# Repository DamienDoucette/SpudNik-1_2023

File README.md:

# SpudNik-1_2023
 Repo for the development of the control software for the UPEI CubeSat Project 2023S

 Created by Damien Doucette
 dldoucette@upei.ca
 damien.doucette01@gmail.com

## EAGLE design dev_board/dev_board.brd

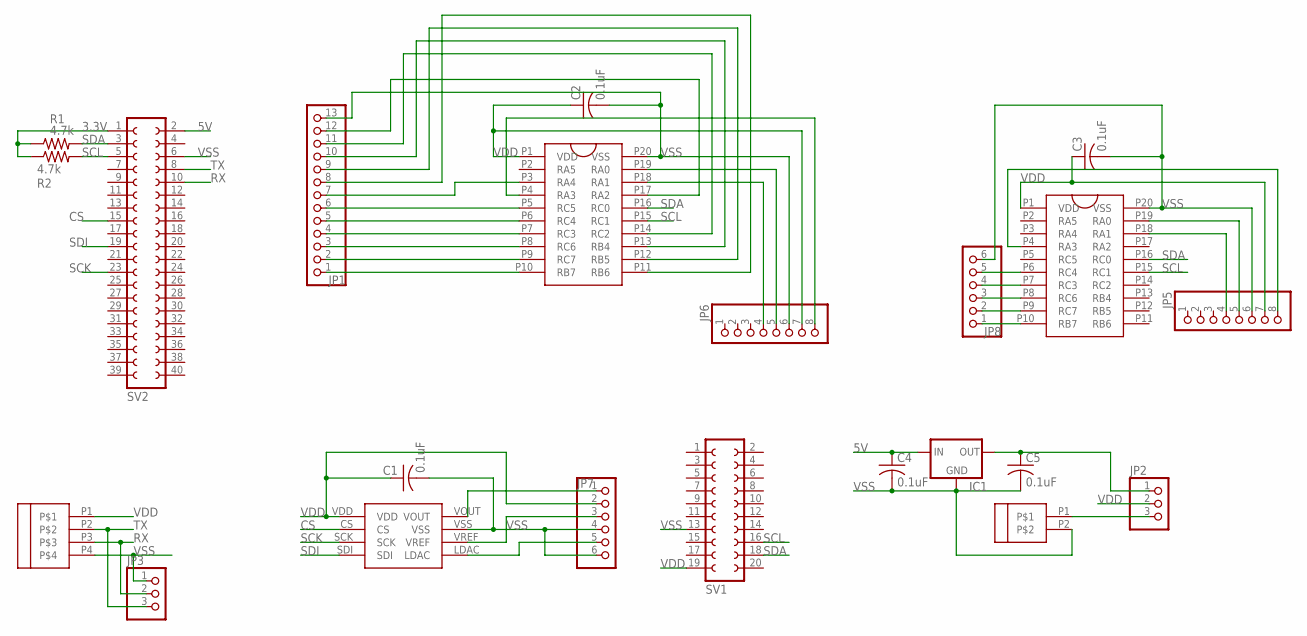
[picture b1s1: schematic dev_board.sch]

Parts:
C1, C2, C3, C4, C5: 0.1uF; C025-030X050
IC1: MCP1700INLINE; TO92-INLINE
JP1: PINHD-1X13; 1X13
JP2, JP3: PINHD-1X3; 1X03
JP5, JP6: PINHD-1X8BIG; 1X08-BIG
JP7, JP8: PINHD-1X6; 1X06
R1, R2: 4.7k; 0207/7
SV1: FE10-2
SV2: FE20-2
U1, U2: PIC18F15Q40PDIP; PDIP
U$1: MCP4911; DAC_DIP
U$2: 4TERMBLOCK
U$3: 2TERMBLOCK

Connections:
3.3V: R1.1, R2.1, SV2.1
5V: C4.1, IC1.2 (IN), SV2.2
CS: SV2.15, U$1.CS
unnamed: JP1.1, U1.P10 (RB7)
unnamed: JP1.2, U1.P9 (RC7)
unnamed: JP1.3, U1.P8 (RC6)
unnamed: JP1.4, U1.P7 (RC3)
unnamed: JP1.5, U1.P6 (RC4)
unnamed: JP1.6, U1.P5 (RC5)
unnamed: JP1.7, U1.P3 (RA4)
unnamed: JP6.8, U1.P4 (RA3)
unnamed: JP1.8, U1.P11 (RB6)
unnamed: JP2.3, U$3.P1
unnamed: JP6.5, U1.P19 (RA0)
unnamed: JP8.1, U2.P10 (RB7)
unnamed: JP8.2, U2.P9 (RC7)
unnamed: JP8.3, U2.P8 (RC6)
unnamed: JP8.4, U2.P7 (RC3)
unnamed: JP8.5, U2.P6 (RC4)
unnamed: JP6.4, U1.P18 (RA1)
unnamed: JP1.9, U1.P12 (RB5)
unnamed: JP1.10, U1.P13 (RB4)
unnamed: JP5.8, U2.P4 (RA3)
unnamed: JP5.5, U2.P19 (RA0)
unnamed: JP5.4, U2.P18 (RA1)
unnamed: JP7.5, U$1.LDAC
unnamed: JP1.11, U1.P14 (RC2)
unnamed: JP7.1, U$1.VOUT
unnamed: JP1.12, U1.P17 (RA2)
unnamed: JP7.3, U$1.VREF
unnamed: C5.1, IC1.3 (OUT), JP2.1
RX: JP3.2, SV2.10, U$2.P3
SCK: SV2.23, U$1.SCK
SCL: R2.2, SV1.16, SV2.5, U1.P15 (RC1), U2.P15 (RC1)
SDA: R1.2, SV1.18, SV2.3, U1.P16 (RC0), U2.P16 (RC0)
SDI: SV2.19, U$1.SDI
TX: JP3.3, SV2.8, U$2.P2
VDD: C1.1, C2.1, C3.1, JP2.2, JP5.7, JP6.7, JP7.2, SV1.19, U1.P1 (VDD), U2.P1 (VDD), U$1.VDD, U$2.P1
VSS: C1.2, C2.2, C3.2, C4.2, C5.2, IC1.1 (GND), JP1.13, JP3.1, JP5.6, JP6.6, JP7.4, JP7.6, JP8.6, SV1.13, SV2.6, U1.P20 (VSS), U2.P20 (VSS), U$1.VSS, U$2.P4, U$3.P2

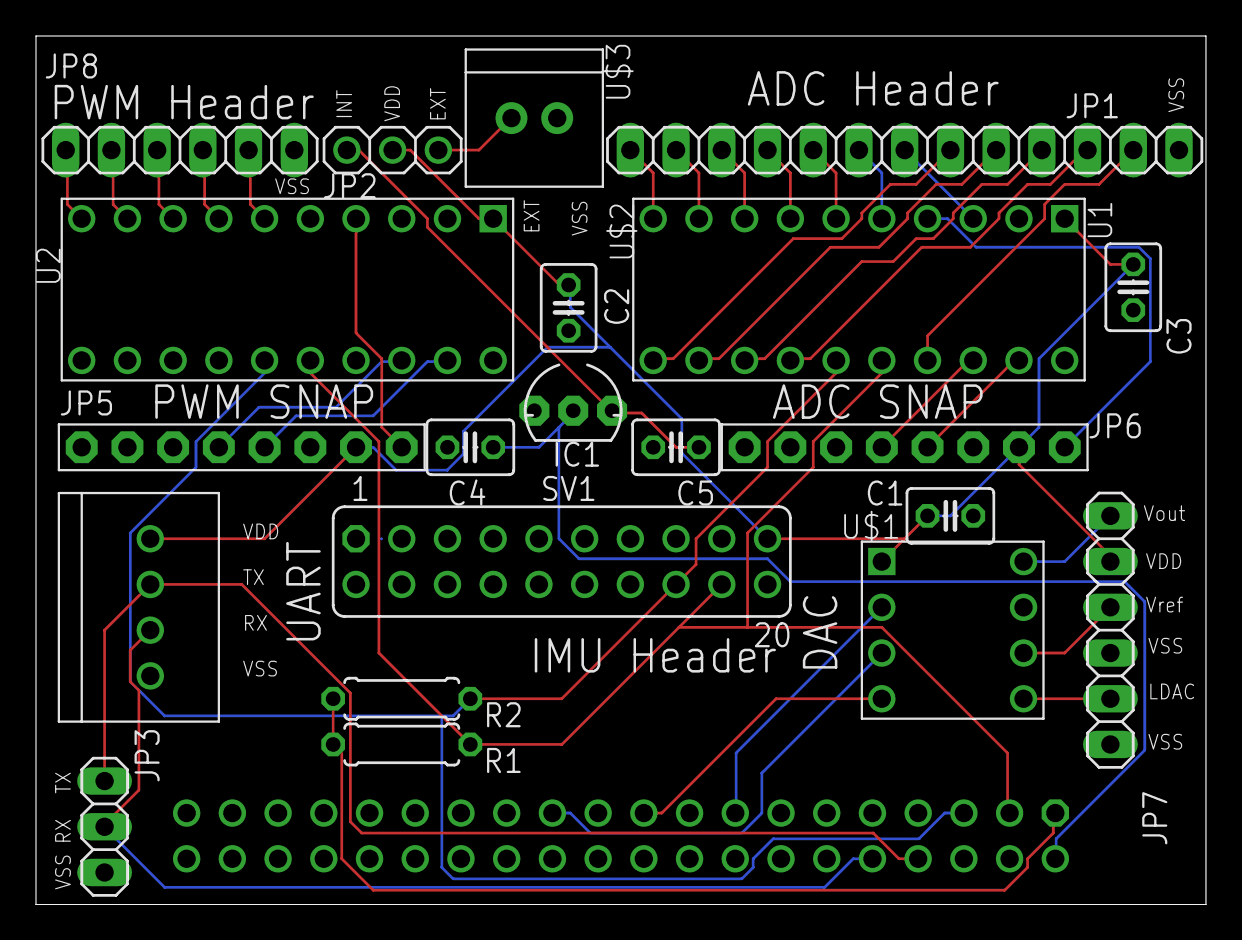
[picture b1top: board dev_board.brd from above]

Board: 2 copper layers, 65.0 x 48.2 mm, 22 parts (1 on the bottom side), 39 nets.

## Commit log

2023-06-06 Started laying out C++ code for control system
    Starting laying out the C++ control software based off the "0. Main.drawio" flowchart.
    Plan to separate the functions of a given thread into separate files for organization.
    I am having trouble getting external files to be compiled with the main file.
    I tried modifying the ".vscode\tasks.json" to include the external file names but was unsuccessful
2023-06-06 Compiler instructions
    Updated so that the separate function files will be linked by the compiler
2023-06-06 Update main.cpp
    Added the function for the ACS thread and put an outline for the logic from the flowchart.
    Variable types and sizes will need to be fixed when I have a better understanding of what is going on.
    Got the thread to function properly in the main function
2023-06-06 Create main.exe
    Compiled version of main.cpp
2023-06-06 Update acs.cpp
    Added separate functions for readTargetAttitudeCOMMS and readTargetAttitudeIMG
    In addition added placeholders for the remaining functions/processes that are called in the ACS thread
2023-06-06 Update acs.h
    Separated the readTargetAttitudeCOMMS and readTargetAttitudeIMG into separate functions
2023-06-07 Create launch.tle
    Test file to hold TLE data copied from the wiki on TLE format
2023-06-07 Update main.cpp
    Added thread for the powerManagement function
    Added empty functions for the other threads.
2023-06-07 Update acs.cpp
    Started laying out the sensingAndEstimation function,
    But then I got confused by what the flowchart was saying
2023-06-07 Update acs.h
    Added arguements to sensingAndEstimation based off the flowchart of the function
2023-06-07 Create powerManagement.cpp
    Created a .cpp file for the function contained under the powerManagement thread
    Started laying out the checkBattery function
2023-06-07 Create powerManagement.h
    Created .h file for the powerManagement thread
2023-06-07 Update tasks.json
    Added file path to the SGP4 files I found
2023-06-07 Added SGP4 Library
    I found a library that is supposed to complete some of the functions outlined in the ADCS Document
    The source for these files is linked in the README.txt file
2023-06-07 Update acs.h
    Added Libraries for I2C Communication specified here:
    https://raspberry-projects.com/pi/programming-in-c/i2c/using-the-i2c-interface
2023-06-07 Update acs.cpp
    Added the foundation for the I2C communication to the IMU and the MCU.
    As this interfaces with the hardware of the PI, I can not test this on my PC. Similarly there are library issues as the specified libraries aren't on my Windows PC.
2023-06-07 Update acs.cpp
    Added method of converting 12 analog readings from sun sensors to the x-y value for each sensor.
    Changed printf statements to include "LOG" or "ERROR" prefix. Would still like to use an actual logging system at some point but this will work for debugging when I get to that stage.
2023-06-07 Update main.cpp
    Added "LOG" to printf statements.
    Would like to use a read logger at some point but this will work for debugging for the time being.
2023-06-08 Create i2c class
    Created the header and cpp file for a I2C class. The hope is that I will be able to reuse the code for different slaves by creating an object for each one
2023-06-08 Motor Driver Library
    Created a simple motor driver library based off the motor driver outlined in the basecamp
    Has not been tested
2023-06-22 Created magnetorquer library
2023-06-22 Modified motorDriver library
    Changed GPIO libraries and updated accordingly
2023-06-22 Create ADC project
    This is a MPLAB X IDE project to configure the ADC on the PIC18F15Q40 Microchip MCU
    This script only connects the ADC to a single pin and reads the value.
2023-06-22 Create 12 Channel ADC script
    This is a MPLAB X IDE project for the PIC18F15Q40 MCU.
    This script allows for the ADC to be connected 12 different IO pins and read an analog signal.
2023-06-22 Create Dual PWM Script
    This is a MPLAB X IDE project for the PIC18F15Q40 MCU.
    This script configures one of the three PWM modules on the board and generates a dual PWM output from this module.
2023-06-22 Create I2C Script
    ************UNDER DEVELOPMENT******************
    This is a MPLAB X IDE project for the PIC18F15Q40 MCU.
    It is to configure and use the I2C module on the MCU
2023-06-22 Create PWM script
    This is a MPLAB X IDE project for the PIC18F15Q40 MCU.
    This script was to configure and use the PWM of the CCP module on the MCU.
    It was determined that this is not the optimal way of creating the PWM signal. The method used in the 'DUAL_PWM' project should be used
2023-06-28 Create Library for I2C communication
    Create library to give readBus and writeBus functions for I2C
    Tested using oscilloscope and it appears to function properly. The digital logic on the SDA and SCL lines appear correct.
    Have not tested with MCU to ensure functionality
2023-06-28 Moved files
    These files were moved to the 'i2c-lib' folder
2023-06-28 Create i2c-lib_TEST.cpp
    Test script to test the functionality of the i2c-lib library
2023-06-28 Moved files to a folder
2023-06-28 Create library for reading ADC values from PIC
    Not tested yet
2023-06-28 Create library for writing PWM values to PIC
    Not tested yet.
2023-06-28 Create MPLAB project for the PWM PIC chip
    Created MPLAB X IDE project for the PWM chips.
    Work in progress, not completed
    Was able to create a fucntion that would take the PWM duty cycle register and duty cycle as parameters and change the duty cycle of any of the three PWM modules
2023-06-30 Create Example.cpp
    Created an example script on how to use the i2c library I created
2023-06-30 Update i2c-lib
    Changed the library so that the read function would take a pointer as a parameter and store the data there, as opposed to returning a pointer to a memory address.
2023-06-30 Create README.md
    Created a document to outline the i2c-lib and how to use it
2023-06-30 Create Example.cpp
    Created an example script to show how to use the picADC library
2023-06-30 Update picADC-lib
    Changed the readSenSensors function to take a pointer to an address as an argument and then save the readings there as opposed to returning a pointer.
2023-06-30 Create README.md
    Created a readme doc to document all information about the picADC library
2023-06-30 Create picADCpicPWM_TEST.cpp
    Test script to simulate reading the ADC values and writing a PWM signal
2023-06-30 Create Example.cpp
    Created an example script on how to use the picPWM library
2023-06-30 Updated picPWM-lib
    Changed methods to void instead of int
2023-06-30 Create README.md
    Created a readme for the picPWM-lib
2023-06-30 Change DUAL_PWMproject
2023-06-30 Change ADC12CH project
2023-06-30 Changes to I2C project
2023-06-30 Changes to PWM project
2023-06-30 Make sunSensor project
    MPLAB X IDE project for the PIC that will read the sun sensor data
2023-06-30 Moved test scripts to vault
2023-07-21 Create library for IMU
    I created a library for the ICM 20948 IMU that was selected to be used. This library is to interface the device with the raspberry pi with a simple interface
2023-07-21 Modified I2C library
    Added a method to do a read/write combined. This was required for the IMU as you have to write the address of the register, then send a new start condition and read back the contents of the register
2023-07-21 Not relevant
2023-07-21 Modify I2C PIC script
2023-07-21 Create I2C script to use DMA
2023-07-21 Create PIC program for UART
2023-07-21 I2C on PIC using the DMA
2023-07-31 Update imu.cpp
    Found a bug with the ACCEL_OFFSET function
2023-07-31 Update picADC-lib
2023-07-31 EXTOSC PIC script
    PIC test script to connect to an external ocsillator
2023-07-31 Update I2C PIC script
2023-07-31 Update sunSensor PIC script
    Updated the script to include the most recent development on the I2C. Was able to test and read all 12 ADC channels on the RPI
2023-07-31 Update actuators script
    Added the most recent I2C development to the actuators script
2023-07-31 Update UART script
    Test script for using the UART on the PIC. Transmitting from PIC is programmed, receiving on the PIC is not.
2023-08-01 Update UART PIC script
    I updated the UART PIC script to allow the PIC to receive data. I tested this using Putty on my PC and the Intempco DTG PKIT-2 USB converter. I have the script constantly writing "testing " to the se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
    I tested this and both functions seem to be working perfectly.
2023-08-01 Update actuators PIC script
    Updated the script that will control the PWM on the PIC from the I2C
2023-08-15 Added Cell Balancing
    These are the design documents regarding the cell balancing circuit.
    This includes:
    - para Matlab file that contains the component values
    - simulink model based on derived transfer function
    - simulink model based on simscape model of circuit
2023-08-15 Remove files that are not used
    I removed some files that I had previously created.
    However the design has changed and these files are no longer used. To avoid confusion, they will be removed.
2023-08-15 Modified PWM library
    PWM library added a delay after successful transaction to allow the PIC time to update the PWM before getting interrupted with another I2C start condition
2023-08-15 Corrected Comments
2023-08-15 Create CellBalancingTest script for the PIC
    This script was created for testing the Cell Balancing circuit. This is not intended to be the final software on the satellite.
    To date it has not been tested
2023-08-15 Create hardwareTesting.cpp
    Create test script for when the development board is ready and all peripherals can be connected
2023-08-15 Ignore
2023-08-15 Updated Comments
2023-08-15 Update UART
    Just changed the test message to be displayed
2023-08-15 Re-Organized
2023-08-15 Added Cell balancing parts list and schematic
2023-08-15 Added Dev board files
2023-08-17 Update picPWM.cpp
    Increase the sleep time to allow for time for PWM to be set
2023-08-17 Update actuators
    Fixed bugs:
    - watchdog was reseting chip
    - Some code that was supposed to be within the condition defining when the chip was called was outside of the condition
    -
2023-08-17 Changed DualPWM
    I was just debugging something else and modified to script for that. Nothing significant changed
2023-08-17 Update sunSensors
    Changed address to be different from PWM chip
    Cleared watchdog timer to prevent resets
    Added extra condition to entering read mode in case timeout occured
2023-08-17 Create compile.sh
    This is a shell script that will compile the hardwareTesting.cpp file
2023-08-17 Update PWM lib
    Allow for 16bit duty cycles
2023-08-17 Update picPWM.cpp
    Fixed bug
2023-08-17 Update Actuators
    Change the PWM script to allow 16bit duty cycles to come over the bus
2023-08-17 Update comments
2023-08-17 Update actuators
2023-08-17 Update sunSensors
2023-08-17 Update main.c
    Updated comment to outline how to change max duty cycle and frequency
2023-08-22 Update Example.cpp
    Updated I2C address of PIC chip
2023-08-22 Update Example.cpp
    Changed I2C address
2023-08-23 Update Example.cpp
    Changed print statements to be more dynamic
2023-08-25 Ignore - Updated files generated when code was ran
2023-08-25 Update CellBalancingTest
    Updated the cell balancing test
    - Fixed some bugs with the switch case conditions being backwards
    - Added a UART interface to allow data to be logged during testing
    - Corrected the PWM period so that it generates the desired frequency
2023-08-25 Logbook Entries
2023-09-08 Create RPI_backup
